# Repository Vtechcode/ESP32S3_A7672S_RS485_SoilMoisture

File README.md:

# ESP32-S3 + A7672S + RS485 Soil Moisture Node

A KiCad-designed IoT board that reads an RS485 soil sensor and sends the data over 4G LTE. It combines an **ESP32-S3** microcontroller, an **A7672SA** LTE Cat-1 modem with GNSS, and an **RS485** transceiver, all powered from a single DC input. It is built for remote soil monitoring in places with no Wi-Fi.

> **Status:** prototype, not yet fabricated or tested. <!-- TODO: update once boards arrive -->

## Features

- **ESP32-S3-WROOM-2** with Wi-Fi and Bluetooth LE, plus USB-C for programming and debugging
- **A7672SA** 4G LTE Cat-1 modem with GNSS, SIM socket, and two U.FL antenna connectors for LTE and GNSS, plus one more U.FL connector (BT_ANT) on the ESP32 side
- **RS485 interface** (MAX3485) on a screw terminal, with a 120 Ω termination switch and SM712 TVS surge protection
- **Three power rails** from one DC input: an LM2596S-5 buck converter (5 V), an AMS1117-3.3 LDO (3.3 V) for the ESP32 side, and a MIC29302 LDO (adjustable) for the modem supply (4V2)
- **Level shifting** between the ESP32 (3.3 V) and the modem (1.8 V) with a TXB0108
- **Protection:** ESD diodes on USB, SIM and RS485, plus TVS diodes on the supply
- **Usability:** reset and boot buttons, status LEDs, test points on the power rails, and 2×9 GPIO breakout headers
- **Assembly-friendly:** 2-layer board, all SMT parts on the top side, JLCPCB-compatible

## Block diagram

```
DC IN ──► LM2596S-5 ──► 5V ──┬─► AMS1117-3.3 ──► 3V3 ──► ESP32-S3 ◄── USB-C
                             └─► MIC29302 ─────► 4V2 ──► A7672SA ── SIM / LTE / GNSS
                                                              ▲
                              ESP32-S3 ◄─ TXB0108 (3V3↔1V8) ──┘
                                  │
                                  └─ UART ─► MAX3485 ─► RS485 terminal ─► soil sensor
```

## Layout

## Schematics

The design is split into four sheets.

**Power** (5 V buck, 3.3 V LDO, modem supply, protection)

**ESP32-S3** (module, USB-C, buttons, LEDs, GPIO headers)

**A7672S** (LTE modem, SIM, level shifter, antennas)

**RS485** (MAX3485, termination, surge protection)

## Target sensor

Designed for the **SenseCAP S-Temp&VWC&EC-02** soil sensor (temperature, volumetric water content and electrical conductivity) over RS485.

<!-- TODO: add sensor supply voltage, baud rate, and Modbus address/register map you use -->

## Repository layout

| Folder | Contents |
|---|---|
| `ESP32S3_A7672S_RS485_SoilMoisture/` | KiCad 9 project: schematics (`power`, `ESP32S3`, `A7672S`, `MAX485_RS485`) and PCB layout |
| `Mfr/` | Manufacturing files: Gerbers, drill files, BOM and CPL for JLCPCB |
| `images/` | Renders and screenshots |

## Board specifications

| | |
|---|---|
| Size | 81.5 × 111.3 mm |
| Layers | 2 |
| Assembly | Single-sided SMT (top), through-hole parts hand-soldered |
| Mounting | 4 × M3 holes |
| Design tool | KiCad 9 |

## Ordering the board

1. Upload the Gerber zip from `Mfr/` to JLCPCB.
2. Choose SMT assembly, top side, and upload the BOM and CPL.
3. Through-hole parts (screw terminals, pin headers, DIP switch) are not placed by SMT assembly. Solder them by hand or select JLCPCB's through-hole option.

## Getting started

<!-- TODO: fill in once firmware exists -->
1. Connect the DC supply to the power screw terminal. <!-- TODO: state the input voltage range -->
2. Insert a SIM card and attach the LTE and GNSS antennas **before** powering on.
3. Wire the soil sensor to the RS485 terminal (A, B, GND and sensor supply).
4. Connect USB-C to flash the ESP32-S3.

## Pin assignments

<!-- TODO: add a table of ESP32-S3 GPIOs for modem UART, modem power key/reset, RS485 TX/RX/DE, LEDs -->

## Firmware

<!-- TODO: link firmware repo or describe planned stack (ESP-IDF / Arduino, AT-command library, Modbus library, MQTT/HTTP endpoint) -->

## License

<!-- TODO: choose one, e.g. CERN-OHL-P-2.0 for hardware, MIT for firmware -->

## Author

Victor Waburi ([@Vtechcode](https://github.com/Vtechcode))

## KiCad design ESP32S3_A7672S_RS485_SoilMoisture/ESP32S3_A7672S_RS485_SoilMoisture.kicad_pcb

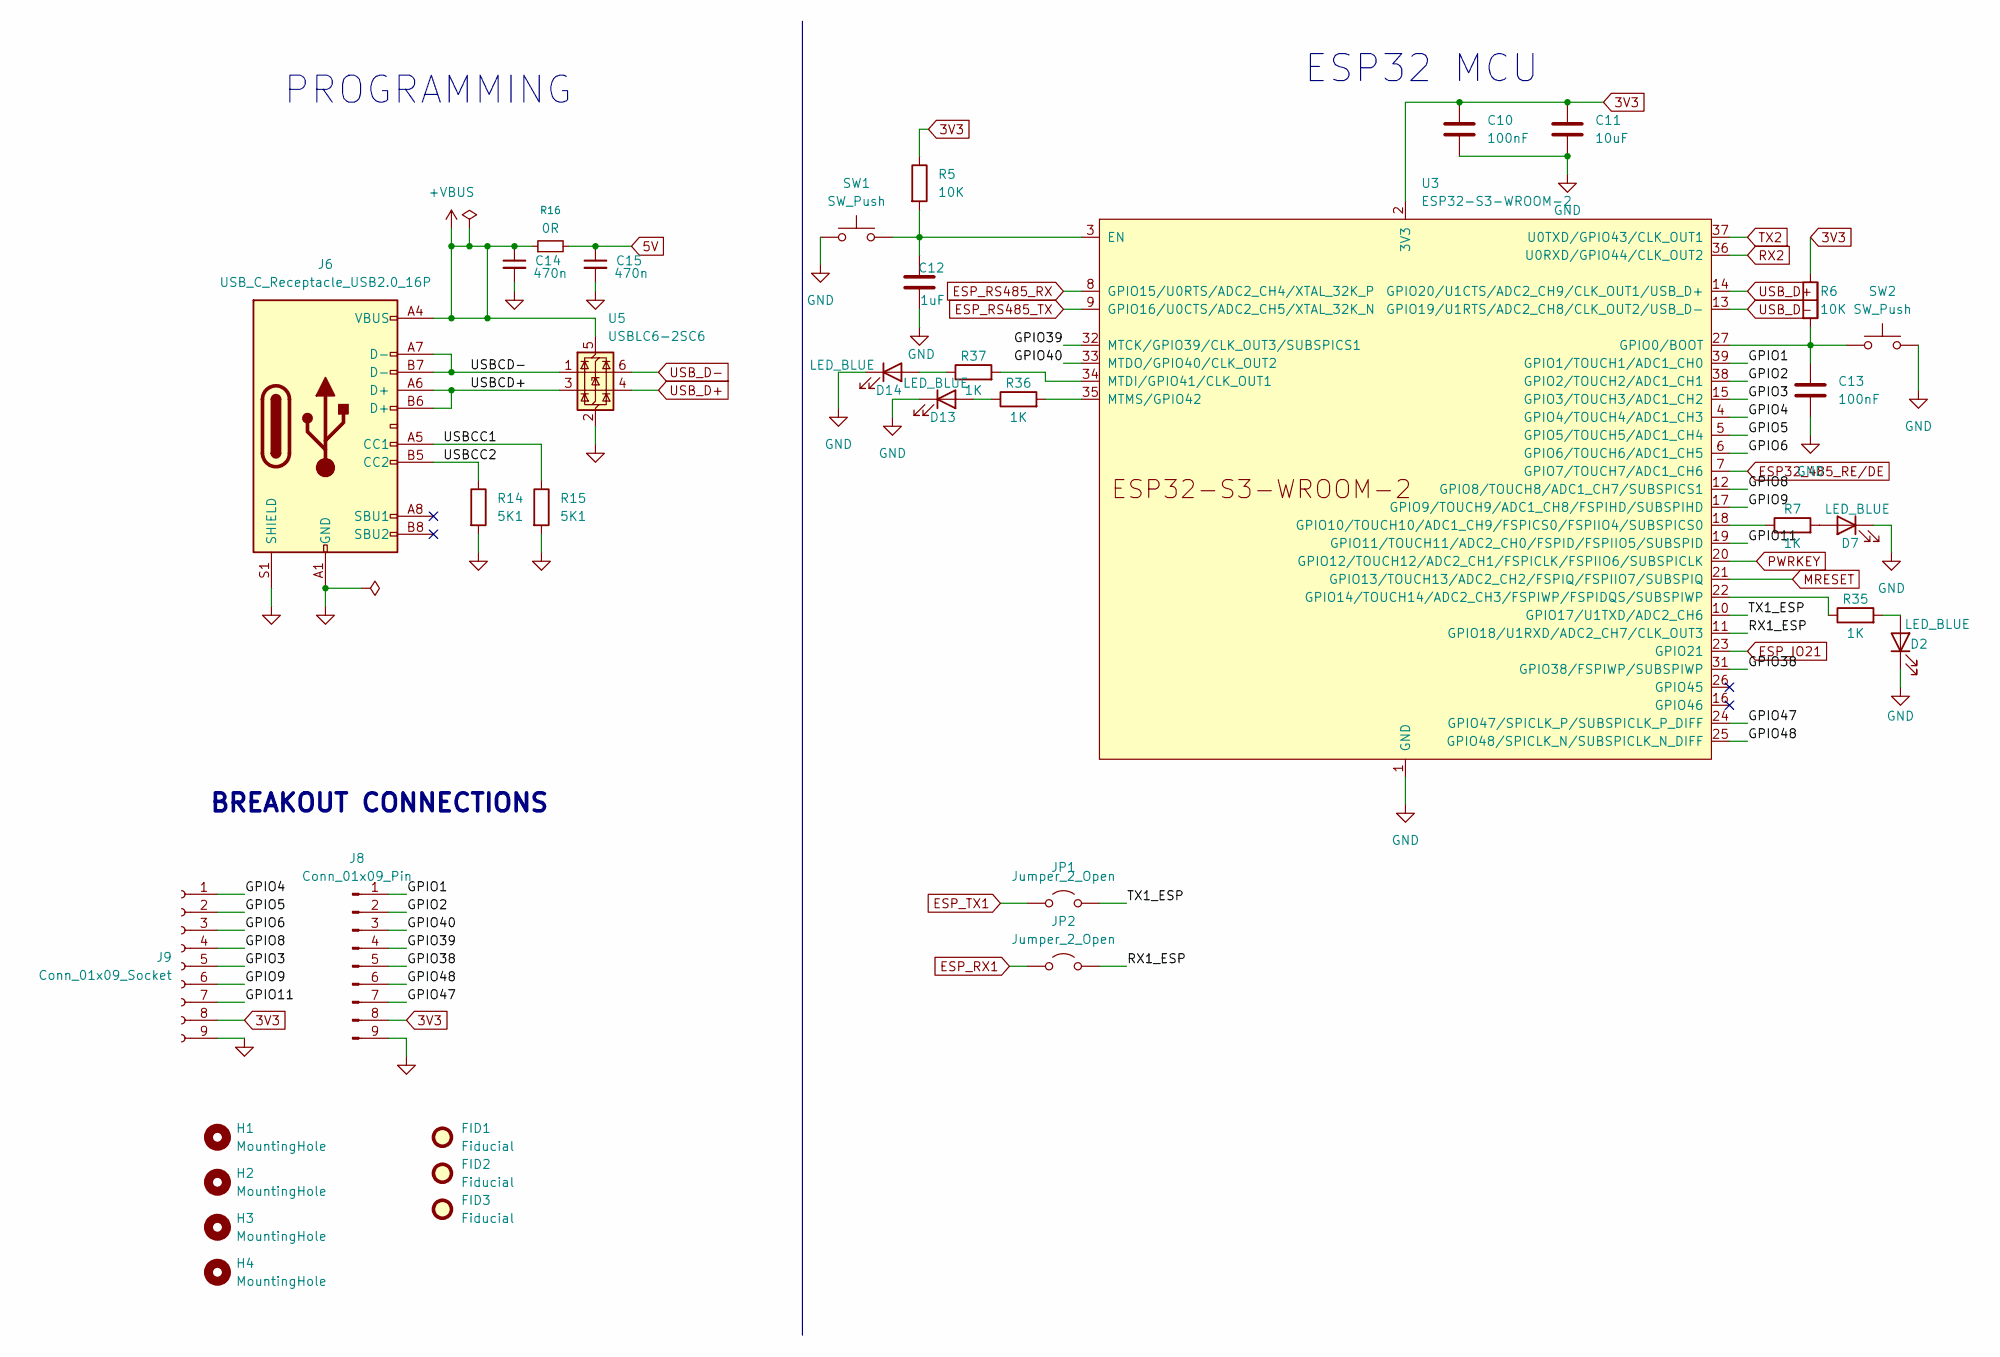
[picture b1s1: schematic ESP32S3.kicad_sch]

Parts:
C10, C13: 100nF; C_0603_1608Metric_Pad1.08x0.95mm_HandSolder; LCSC number C16194197
C11: 10uF; C_0603_1608Metric_Pad1.08x0.95mm_HandSolder; LCSC number C109457
C12: 1uF; C_0603_1608Metric_Pad1.08x0.95mm_HandSolder; LCSC number C29936
C14, C15: 470n; C_0402_1005Metric; LCSC number C364319
D2, D7, D13, D14: LED_BLUE; LED_0805_2012Metric_Pad1.15x1.40mm_HandSolder; LCSC number C5156165
FID1, FID2, FID3: Fiducial; Fiducial_0.5mm_Mask1.5mm
H1, H2, H3, H4: MountingHole; MountingHole_3.2mm_M3
J6: USB_C_Receptacle_USB2.0_16P; USB_C_Receptacle_GCT_USB4105-xx-A_16P_TopMnt_Horizontal; LCSC number C45082766
J8: Conn_01x09_Pin; PinSocket_1x09_P2.54mm_Vertical
J9: Conn_01x09_Socket; PinSocket_1x09_P2.54mm_Vertical
JP1, JP2: Jumper_2_Open; TestPoint_2Pads_Pitch2.54mm_Drill0.8mm
R5, R6: 10K; R_0603_1608Metric_Pad0.98x0.95mm_HandSolder; LCSC number C2479067
R7, R35, R36, R37: 1K; R_0603_1608Metric_Pad0.98x0.95mm_HandSolder; LCSC number C860716
R14: 5K1; R_0603_1608Metric_Pad0.98x0.95mm_HandSolder; LCSC number C123727
R15: 5K1; R_0402_1005Metric; LCSC number C123727
R16: 0R; R_0603_1608Metric; LCSC number C100044
SW1, SW2: SW_Push; SW_SPST_B3U-1000P; LCSC number C428628
U3: ESP32-S3-WROOM-2; LCSC number C42417293
U5: USBLC6-2SC6; SOT-23-6; LCSC number C7519

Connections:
3V3: C10.1, C11.1, J8.8, J9.8, R5.1, R6.1, U3.2 (3V3); also elsewhere on the board
5V: C15.1, R16.2; also elsewhere on the board
+VBUS: C14.1, J6.A4 (VBUS), J6.A9 (VBUS), J6.B4 (VBUS), J6.B9 (VBUS), R16.1, U5.5 (VBUS)
/ESP32S3/GPIO1: J8.1, U3.39 (GPIO1/TOUCH1/ADC1_CH0)
/ESP32S3/GPIO2: J8.2, U3.38 (GPIO2/TOUCH2/ADC1_CH1)
/ESP32S3/GPIO3: J9.5, U3.15 (GPIO3/TOUCH3/ADC1_CH2)
/ESP32S3/GPIO4: J9.1, U3.4 (GPIO4/TOUCH4/ADC1_CH3)
/ESP32S3/GPIO5: J9.2, U3.5 (GPIO5/TOUCH5/ADC1_CH4)
/ESP32S3/GPIO6: J9.3, U3.6 (GPIO6/TOUCH6/ADC1_CH5)
/ESP32S3/GPIO8: J9.4, U3.12 (GPIO8/TOUCH8/ADC1_CH7/SUBSPICS1)
/ESP32S3/GPIO9: J9.6, U3.17 (GPIO9/TOUCH9/ADC1_CH8/FSPIHD/SUBSPIHD)
/ESP32S3/GPIO11: J9.7, U3.19 (GPIO11/TOUCH11/ADC2_CH0/FSPID/FSPIIO5/S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)
/ESP32S3/GPIO38: J8.5, U3.31 (GPIO38/FSPIWP/SUBSPIWP)
/ESP32S3/GPIO39: J8.4, U3.32 (MTCK/GPIO39/CLK_OUT3/SUBSPICS1)
/ESP32S3/GPIO40: J8.3, U3.33 (MTDO/GPIO40/CLK_OUT2)
/ESP32S3/GPIO47: J8.7, U3.24 (GPIO47/SPICLK_P/SUBSPICLK_P_DIFF)
/ESP32S3/GPIO48: J8.6, U3.25 (GPIO48/SPICLK_N/SUBSPICLK_N_DIFF)
/ESP32S3/RX1_ESP: JP2.2 (B), U3.11 (GPIO18/U1RXD/ADC2_CH7/CLK_OUT3)
/ESP32S3/TX1_ESP: JP1.2 (B), U3.10 (GPIO17/U1TXD/ADC2_CH6)
/ESP32S3/USBCC1: J6.A5 (CC1), R15.1
/ESP32S3/USBCC2: J6.B5 (CC2), R14.1
/ESP32S3/USBCD+: J6.A6 (D+), J6.B6 (D+), U5.3 (I/O2)
/ESP32S3/USBCD-: J6.A7 (D-), J6.B7 (D-), U5.1 (I/O1)
ESP32_485_RE/DE: U3.7 (GPIO7/TOUCH7/ADC1_CH6); also elsewhere on the board
ESP_IO21: U3.23 (GPIO21); also elsewhere on the board
ESP_RS485_RX: U3.8 (GPIO15/U0RTS/ADC2_CH4/XTAL_32K_P); also elsewhere on the board
ESP_RS485_TX: U3.9 (GPIO16/U0CTS/ADC2_CH5/XTAL_32K_N); also elsewhere on the board
ESP_RX1: JP2.1 (A); also elsewhere on the board
ESP_TX1: JP1.1 (A); also elsewhere on the board
GND: C10.2, C11.2, C12.2, C13.2, C14.2, C15.2, D2.1 (K), D7.1 (K), D13.1 (K), D14.1 (K), J6.A1 (GND), J6.A12 (GND), J6.B1 (GND), J6.B12 (GND), J6.S1 (SHIELD), J8.9, J9.9, R14.2, R15.2, SW1.1, SW2.2, U3.1 (GND), U3.40 (GND), U3.41 (GND), U5.2 (GND); also elsewhere on the board
MRESET: U3.21 (GPIO13/TOUCH13/ADC2_CH2/FSPIQ/FSPIIO7/S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); also elsewhere on the board
unnamed: D2.2 (A), R35.2
unnamed: D7.2 (A), R7.2
unnamed: D13.2 (A), R36.1
unnamed: D14.2 (A), R37.1
unnamed: C12.1, R5.2, SW1.2, U3.3 (EN)
unnamed: C13.1, R6.2, SW2.1, U3.27 (GPIO0/BOOT)
unnamed: R7.1, U3.18 (GPIO10/TOUCH10/ADC1_CH9/FSPICS0/FSPIIO4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)
unnamed: R35.1, U3.22 (GPIO14/TOUCH14/ADC2_CH3/FSPIWP/FSPIDQS/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)
unnamed: R37.2, U3.34 (MTDI/GPIO41/CLK_OUT1)
unnamed: R36.2, U3.35 (MTMS/GPIO42)
PWRKEY: U3.20 (GPIO12/TOUCH12/ADC2_CH1/FSPICLK/FSPIIO6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); also elsewhere on the board
RX2: U3.36 (U0RXD/GPIO44/CLK_OUT2); also elsewhere on the board
TX2: U3.37 (U0TXD/GPIO43/CLK_OUT1); also elsewhere on the board
USB_D+: U3.14 (GPIO20/U1CTS/ADC2_CH9/CLK_OUT1/USB_D+), U5.4 (I/O2)
USB_D-: U3.13 (GPIO19/U1RTS/ADC2_CH8/CLK_OUT2/USB_D-), U5.6 (I/O1)

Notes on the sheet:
ESP32 MCU
BREAKOUT CONNECTIONS
PROGRAMMING

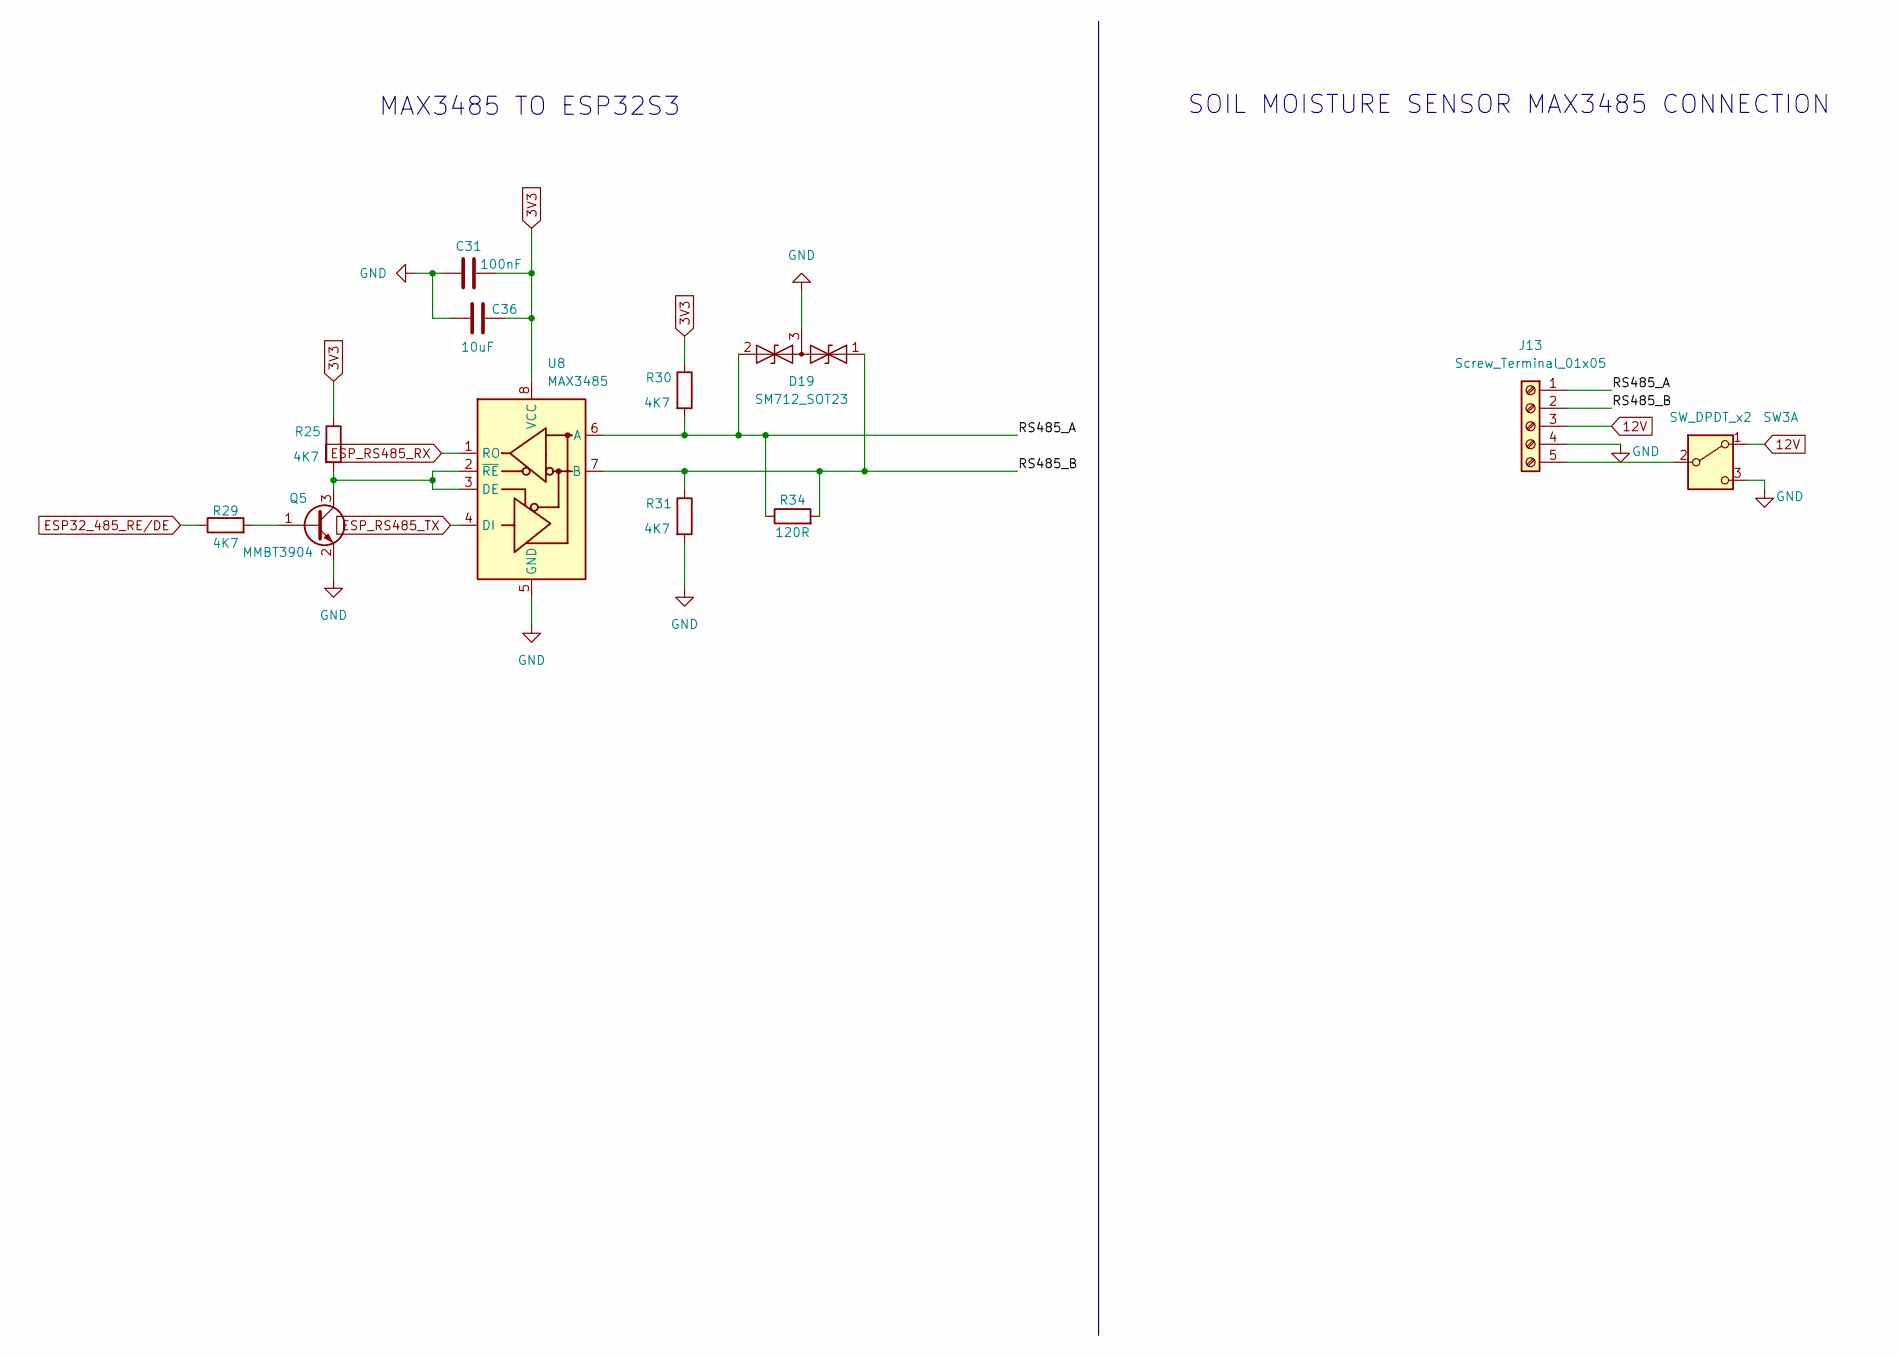
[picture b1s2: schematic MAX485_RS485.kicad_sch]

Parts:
C31: 100nF; C_0603_1608Metric; LCSC number C16194197
C36: 10uF; C_0603_1608Metric; LCSC number C109457
D19: SM712_SOT23; SOT-23; LCSC number C502564
J13: Screw_Terminal_01x05; TerminalBlock_Phoenix_MKDS-1,5-5-5.08_1x05_P5.08mm_Horizont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
Q5: MMBT3904; SOT-23; LCSC number C81464
R25, R29, R30, R31: 4K7; R_0603_1608Metric_Pad0.98x0.95mm_HandSolder; LCSC number C844931
R34: 120R; R_0603_1608Metric_Pad0.98x0.95mm_HandSolder; LCSC number C4307692
SW3: SW_DPDT_x2; SW_CK_JS202011CQN_DPDT_Straight; LCSC number C221663
U8: MAX3485; SOIC-8_3.9x4.9mm_P1.27mm; LCSC number C94609

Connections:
3V3: C31.2, C36.2, R25.1, R30.1, U8.8 (VCC); also elsewhere on the board
12V: J13.3, SW3.1 (A); also elsewhere on the board
/MAX485_RS485/RS485_A: D19.2 (A2), J13.1, R30.2, R34.1, U8.6 (A)
/MAX485_RS485/RS485_B: D19.1 (A1), J13.2, R31.1, R34.2, U8.7 (B)
ESP32_485_RE/DE: R29.1; also elsewhere on the board
ESP_RS485_RX: U8.1 (RO); also elsewhere on the board
ESP_RS485_TX: U8.4 (DI); also elsewhere on the board
GND: C31.1, C36.1, D19.3 (common), J13.4, Q5.2 (E), R31.2, SW3.3 (C), U8.5 (GND); also elsewhere on the board
unnamed: J13.5, SW3.2 (B)
unnamed: Q5.1 (B), R29.2
unnamed: Q5.3 (C), R25.2, U8.2 (~RE), U8.3 (DE)

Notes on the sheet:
MAX3485 TO ESP32S3
SOIL MOISTURE SENSOR MAX3485 CONNECTION

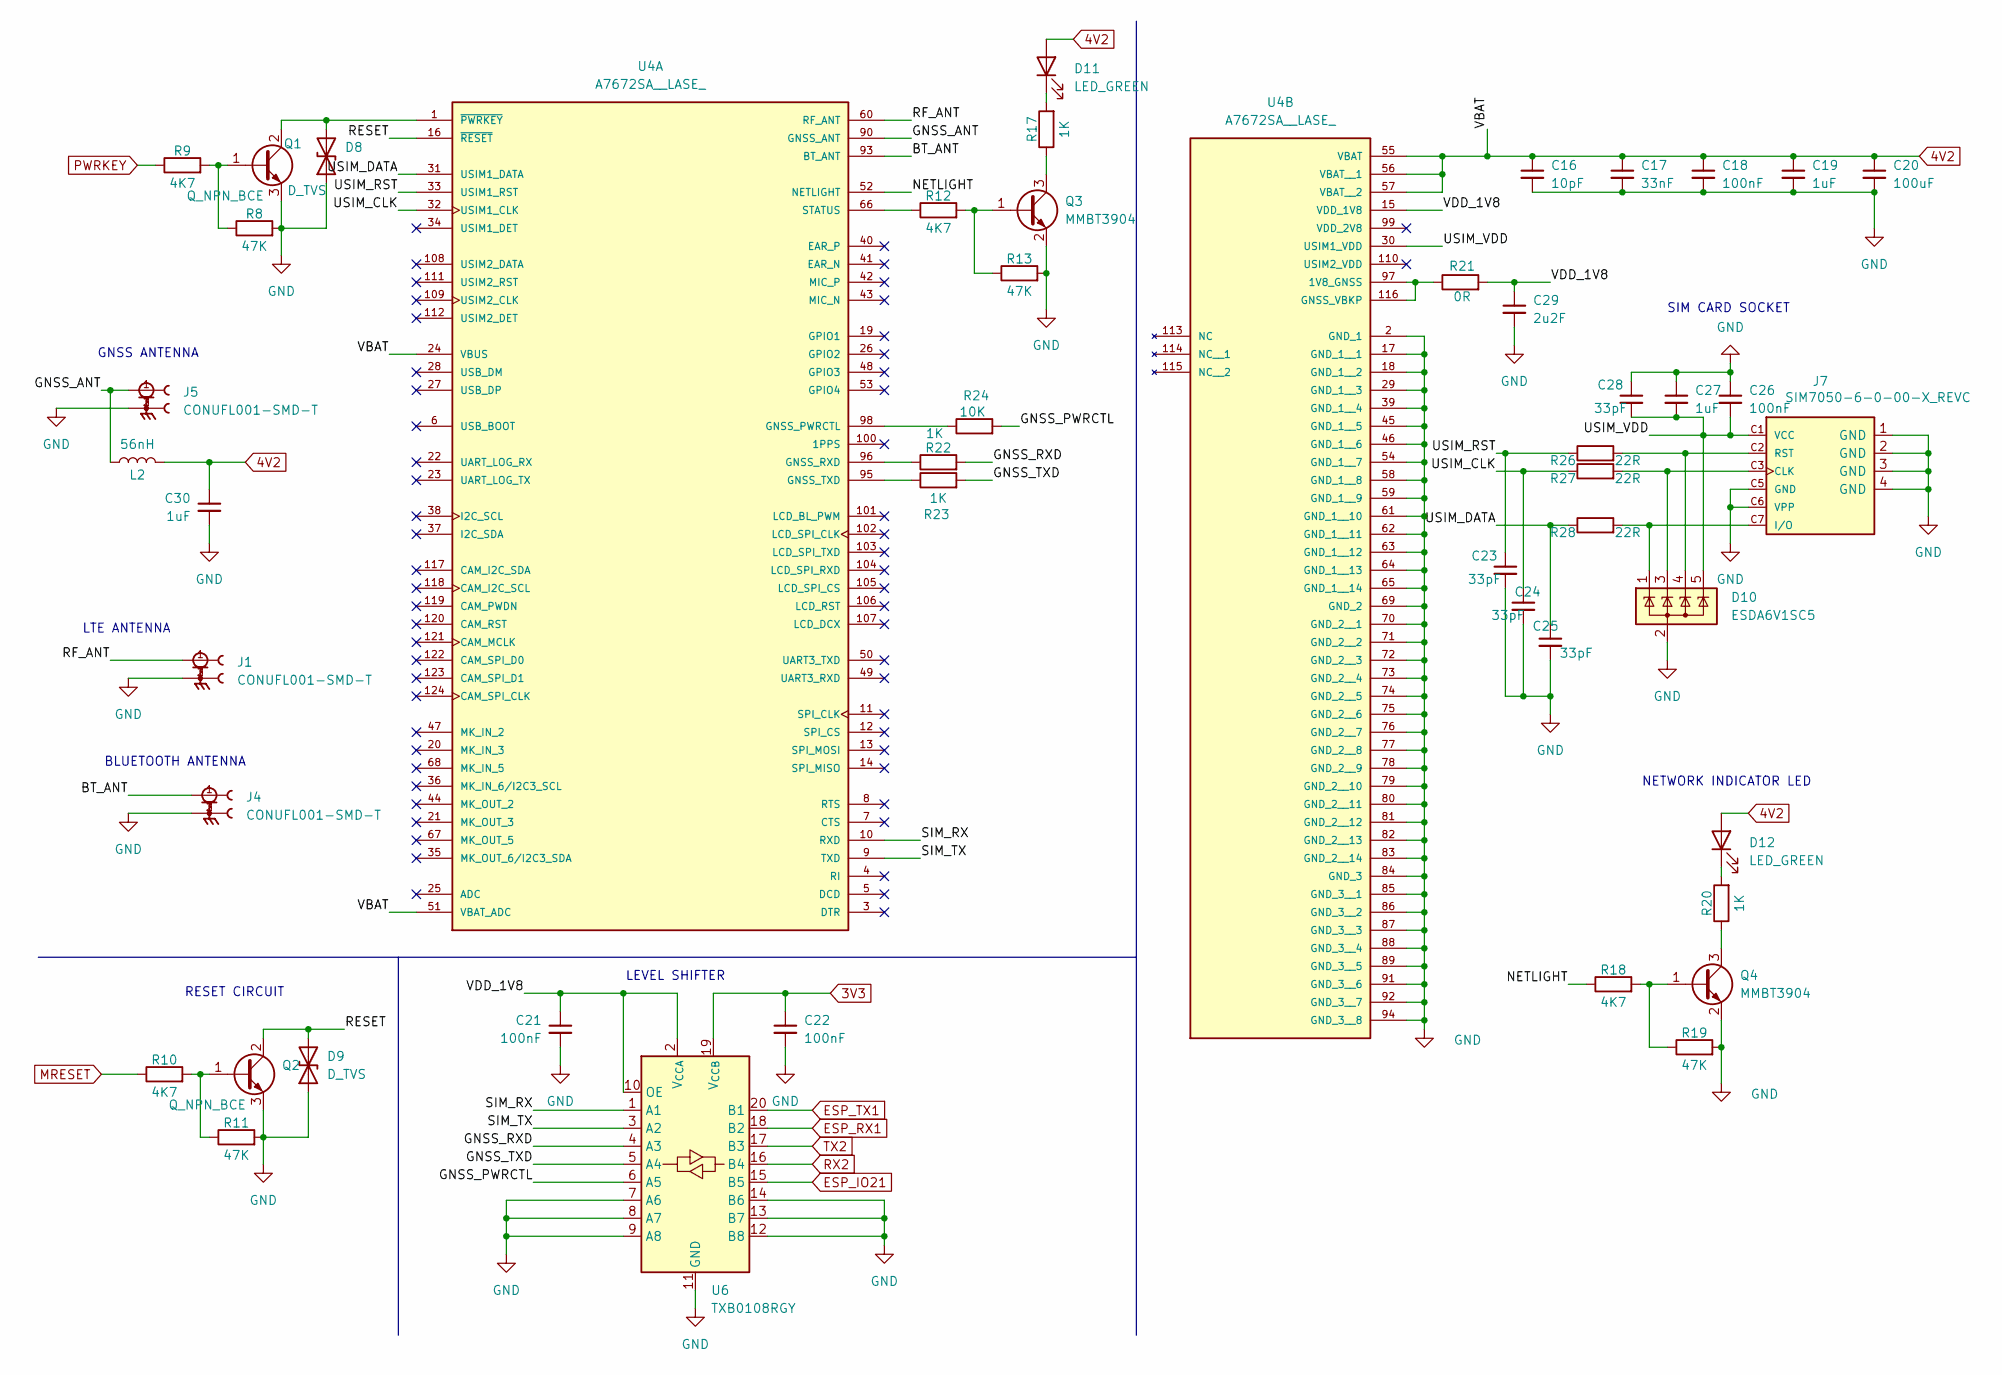
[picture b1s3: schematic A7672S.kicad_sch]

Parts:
C16: 10pF; C_0603_1608Metric_Pad1.08x0.95mm_HandSolder; LCSC number C2167326
C17: 33nF; C_0603_1608Metric_Pad1.08x0.95mm_HandSolder; LCSC number C16194260
C18: 100nF; C_0603_1608Metric_Pad1.08x0.95mm_HandSolder; LCSC number C16194197
C19: 1uF; C_0603_1608Metric_Pad1.08x0.95mm_HandSolder; LCSC number C29936
C20: 100uF; C_0805_2012Metric; LCSC number C141660
C21, C22, C26: 100nF; C_0603_1608Metric; LCSC number C16194197
C23, C24, C25, C28: 33pF; C_0603_1608Metric; LCSC number C1663
C27, C30: 1uF; C_0603_1608Metric; LCSC number C29936
C29: 2u2F; C_0603_1608Metric_Pad1.08x0.95mm_HandSolder; LCSC number C23630
D8, D9: D_TVS; D_SOD-323; LCSC number C5173266
D10: ESDA6V1SC5; SOT-23-5; LCSC number C2935146
D11, D12: LED_GREEN; LED_0805_2012Metric_Pad1.15x1.40mm_HandSolder; LCSC number C5456999
J1, J4, J5: CONUFL001-SMD-T; LINX_CONUFL001-SMD-T; LCSC number C22418213
J7: SIM7050-6-0-00-X_REVC; GCT_SIM7050-6-0-00-X_REVC; LCSC number C7363806
L2: 56nH; L_0603_1608Metric; LCSC number C98079
Q1, Q2: Q_NPN_BCE; SOT-23; LCSC number C513268
Q3, Q4: MMBT3904; SOT-23; LCSC number C81464
R8, R11, R13, R19: 47K; R_0603_1608Metric_Pad0.98x0.95mm_HandSolder; LCSC number C105579
R9, R10, R12, R18: 4K7; R_0603_1608Metric_Pad0.98x0.95mm_HandSolder; LCSC number C844931
R17, R20, R23: 1K; R_0603_1608Metric_Pad0.98x0.95mm_HandSolder; LCSC number C860716
R21: 0R; R_0805_2012Metric_Pad1.20x1.40mm_HandSolder; LCSC number C100045
R22: 1K; R_0603_1608Metric; LCSC number C98079
R24: 10K; R_0603_1608Metric_Pad0.98x0.95mm_HandSolder; LCSC number C2479067
R26, R27, R28: 22R; R_0603_1608Metric; LCSC number C2479410
U4: A7672SA__LASE_; XCVR_A7672SA__LASE_; PARTREV 1.03; LCSC number C5370391
U6: TXB0108RGY; Texas_RGY_R-PVQFN-N20_EP2.05x3.05mm; LCSC number C194701

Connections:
3V3: C22.1, U6.19 (V_{CCB}); also elsewhere on the board
4V2: C16.1, C17.1, C18.1, C19.1, C20.1, C30.1, D11.2 (A), D12.2 (A), L2.2, U4.24 (VBUS), U4.51 (VBAT_ADC), U4.55 (VBAT), U4.56 (VBAT__1), U4.57 (VBAT__2); also elsewhere on the board
/A7672S/BT_ANT: J4.1, U4.93 (BT_ANT)
/A7672S/GNSS_ANT: J5.1, L2.1, U4.90 (GNSS_ANT)
/A7672S/GNSS_PWRCTL: R24.2, U6.6 (A5)
/A7672S/GNSS_RXD: R22.2, U6.4 (A3)
/A7672S/GNSS_TXD: R23.2, U6.5 (A4)
/A7672S/NETLIGHT: R18.1, U4.52 (NETLIGHT)
/A7672S/RESET: D9.2 (A2), Q2.2 (C), U4.16 (~RESET)
/A7672S/RF_ANT: J1.1, U4.60 (RF_ANT)
/A7672S/SIM_RX: U4.10 (RXD), U6.1 (A1)
/A7672S/SIM_TX: U4.9 (TXD), U6.3 (A2)
/A7672S/USIM_CLK: C24.1, R27.1, U4.32 (USIM1_CLK)
/A7672S/USIM_DATA: C25.1, R28.1, U4.31 (USIM1_DATA)
/A7672S/USIM_RST: C23.1, R26.1, U4.33 (USIM1_RST)
/A7672S/USIM_VDD: C26.2, C27.2, C28.2, D10.5 (K), J7.C1 (VCC), U4.30 (USIM1_VDD)
/A7672S/VDD_1V8: C21.1, C29.1, R21.2, U4.15 (VDD_1V8), U6.2 (V_{CCA}), U6.10 (OE)
ESP_IO21: U6.15 (B5); also elsewhere on the board
ESP_RX1: U6.18 (B2); also elsewhere on the board
ESP_TX1: U6.20 (B1); also elsewhere on the board
GND: C16.2, C17.2, C18.2, C19.2, C20.2, C21.2, C22.2, C23.2, C24.2, C25.2, C26.1, C27.1, C28.1, C29.2, C30.2, D8.1 (A1), D9.1 (A1), D10.2 (A), J1.2, J1.3, J4.2, J4.3, J5.2, J5.3, J7.1 (GND), J7.2 (GND), J7.3 (GND), J7.4 (GND), J7.C5 (GND), J7.C6 (VPP), Q1.3 (E), Q2.3 (E), Q3.2 (E), Q4.2 (E), R8.2, R11.2, R13.2, R19.2, U4.2 (GND_1), U4.17 (GND_1__1), U4.18 (GND_1__2), U4.29 (GND_1__3), U4.39 (GND_1__4), U4.45 (GND_1__5), U4.46 (GND_1__6), U4.54 (GND_1__7), U4.58 (GND_1__8), U4.59 (GND_1__9), U4.61 (GND_1__10), U4.62 (GND_1__11), U4.63 (GND_1__12), U4.64 (GND_1__13), U4.65 (GND_1__14), U4.69 (GND_2), U4.70 (GND_2__1), U4.71 (GND_2__2), U4.72 (GND_2__3), U4.73 (GND_2__4), U4.74 (GND_2__5), U4.75 (GND_2__6), U4.76 (GND_2__7), U4.77 (GND_2__8), U4.78 (GND_2__9), U4.79 (GND_2__10), U4.80 (GND_2__11), U4.81 (GND_2__12), U4.82 (GND_2__13), U4.83 (GND_2__14), U4.84 (GND_3), U4.85 (GND_3__1), U4.86 (GND_3__2), U4.87 (GND_3__3), U4.88 (GND_3__4), U4.89 (GND_3__5), U4.91 (GND_3__6), U4.92 (GND_3__7), U4.94 (GND_3__8), U6.7 (A6), U6.8 (A7), U6.9 (A8), U6.11 (GND), U6.12 (B8), U6.13 (B7), U6.14 (B6), U6.21 (GND); also elsewhere on the board
MRESET: R10.1; also elsewhere on the board
unnamed: D8.2 (A2), Q1.2 (C), U4.1 (~PWRKEY)
unnamed: D11.1 (K), R17.2
unnamed: D12.1 (K), R20.2
unnamed: D10.3 (K), J7.C3 (CLK), R27.2
unnamed: D10.1 (K), J7.C7 (I/O), R28.2
unnamed: D10.4 (K), J7.C2 (RST), R26.2
unnamed: Q1.1 (B), R8.1, R9.2
unnamed: Q2.1 (B), R10.2, R11.1
unnamed: Q3.1 (B), R12.2, R13.1
unnamed: Q3.3 (C), R17.1
unnamed: Q4.1 (B), R18.2, R19.1
unnamed: Q4.3 (C), R20.1
unnamed: R24.1, U4.98 (GNSS_PWRCTL)
unnamed: R22.1, U4.96 (GNSS_RXD)
unnamed: R23.1, U4.95 (GNSS_TXD)
unnamed: R12.1, U4.66 (STATUS)
unnamed: R21.1, U4.97 (1V8_GNSS), U4.116 (GNSS_VBKP)
PWRKEY: R9.1; also elsewhere on the board
RX2: U6.16 (B4); also elsewhere on the board
TX2: U6.17 (B3); also elsewhere on the board

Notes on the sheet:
LTE ANTENNA
NETWORK INDICATOR LED
GNSS ANTENNA
SIM CARD SOCKET
RESET CIRCUIT
LEVEL SHIFTER
BLUETOOTH ANTENNA

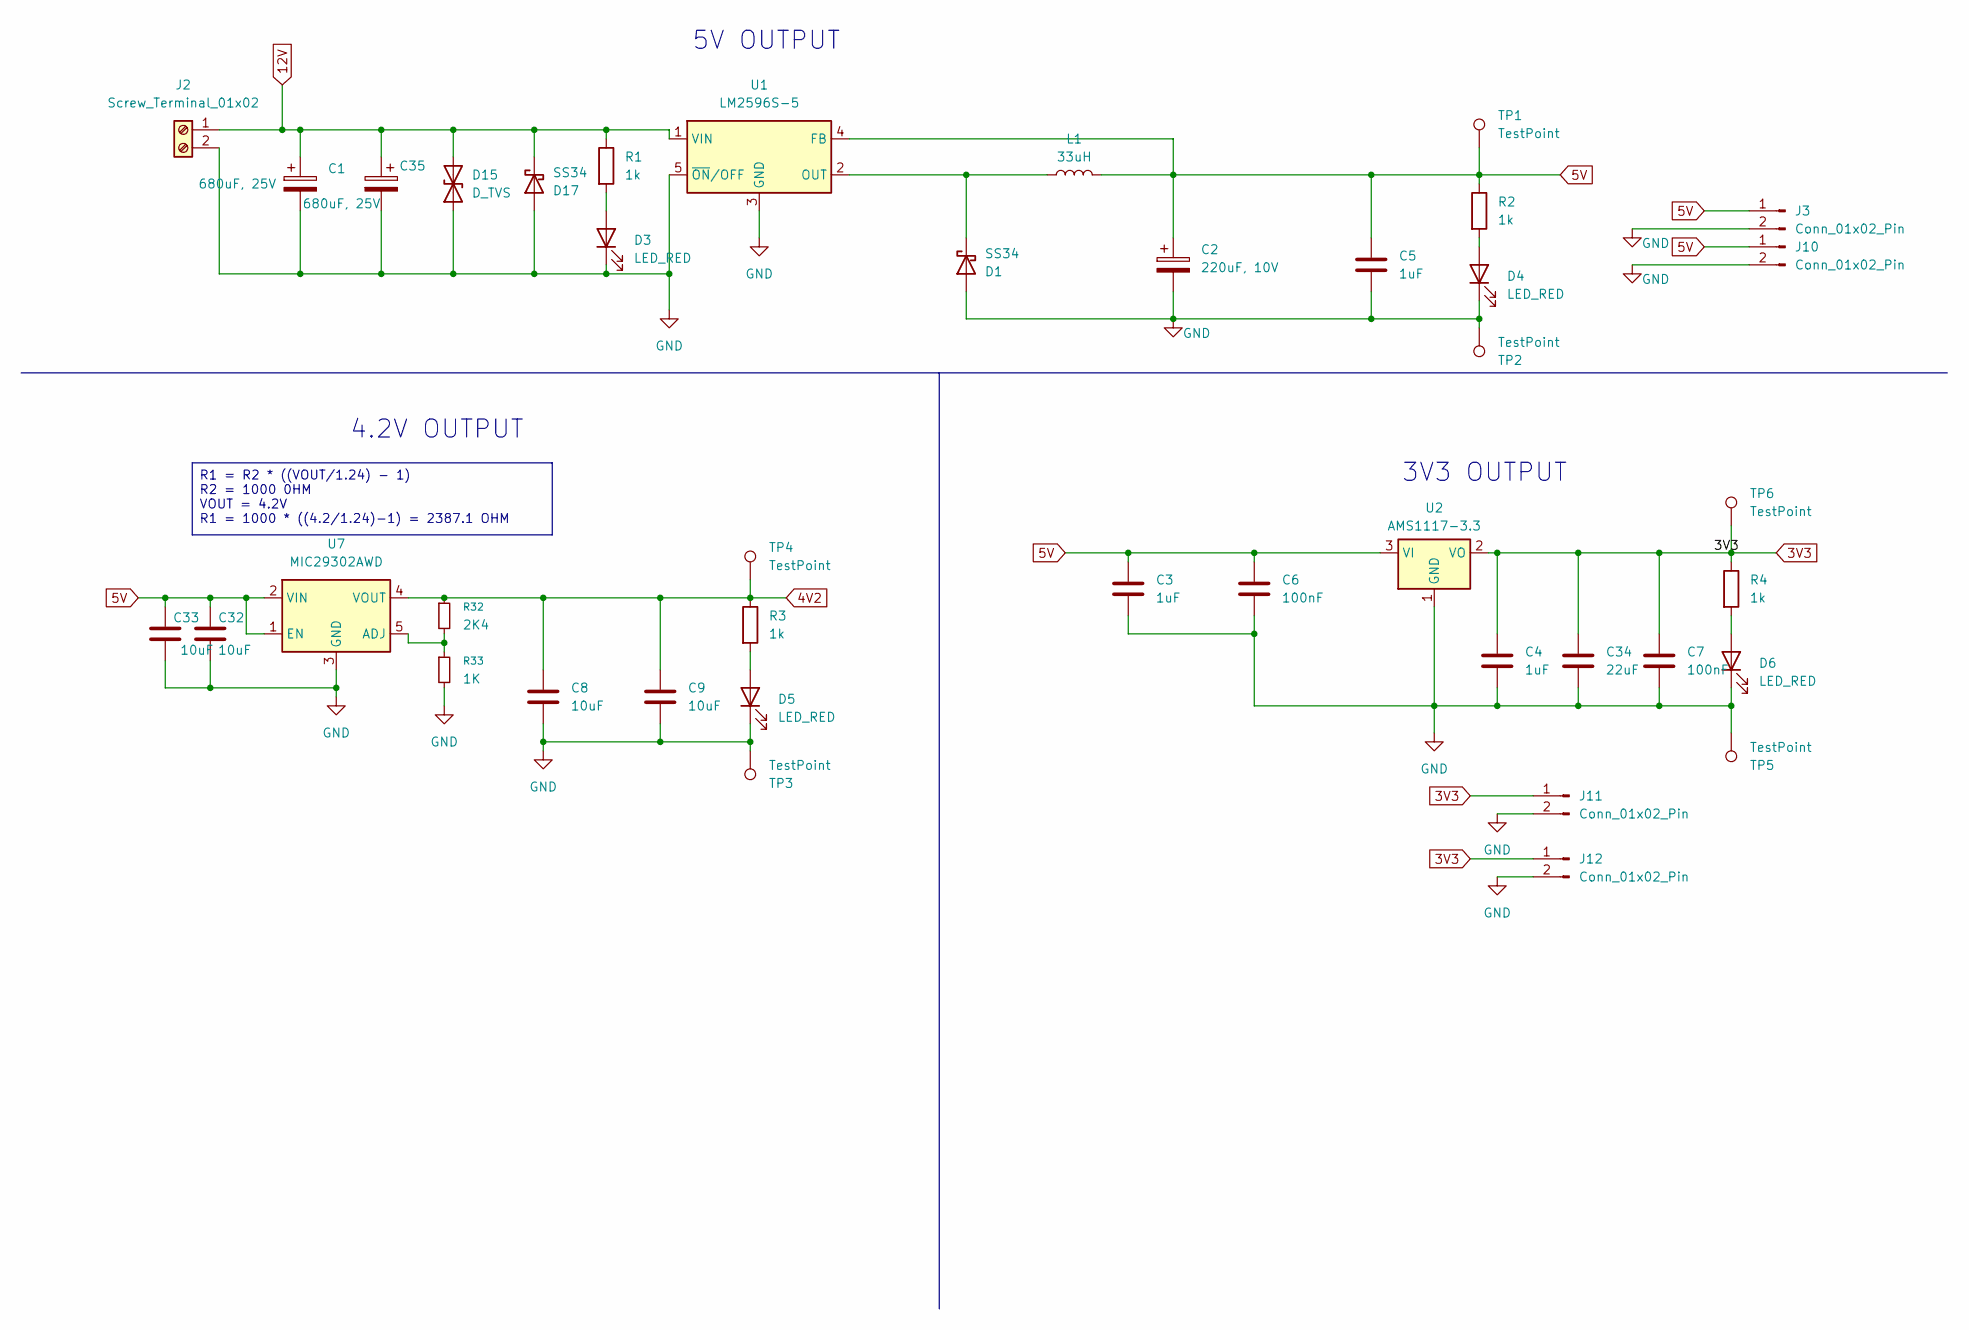
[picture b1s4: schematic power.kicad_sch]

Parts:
C1, C35: 680uF, 25V; CP_Elec_10x7.7; LCSC number C494831
C2: 220uF, 10V; CP_Elec_6.3x7.7; LCSC number C336207
C3, C4, C5: 1uF; C_0603_1608Metric_Pad1.08x0.95mm_HandSolder; LCSC number C29936
C6, C7: 100nF; C_0603_1608Metric_Pad1.08x0.95mm_HandSolder; LCSC number C16194197
C8, C9, C32, C33: 10uF; C_0603_1608Metric_Pad1.08x0.95mm_HandSolder; LCSC number C109457
C34: 22uF; C_0805_2012Metric; LCSC number C128856
D1, D17: SS34; D_SMC; LCSC number C2837271
D3, D4, D5, D6: LED_RED; LED_0805_2012Metric; LCSC number C17440976
D15: D_TVS; D_SOD-128; LCSC number VS12VUA1LAMTR
J2: Screw_Terminal_01x02; TerminalBlock_Phoenix_MKDS-1,5-2-5.08_1x02_P5.08mm_Horizont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; LCSC number C8465
J3, J10, J11, J12: Conn_01x02_Pin; PinHeader_1x02_P2.54mm_Vertical
L1: 33uH; L_7.3x7.3_H4.5; LCSC number C2042589
R1, R2, R3, R4: 1k; R_0603_1608Metric; LCSC number C860716
R32: 2K4; R_0603_1608Metric_Pad0.98x0.95mm_HandSolder; LCSC number C543157
R33: 1K; R_0603_1608Metric_Pad0.98x0.95mm_HandSolder; LCSC number C860716
TP1, TP2, TP3, TP4, TP5, TP6: TestPoint; TestPoint_Pad_D2.0mm
U1: LM2596S-5; TO-263-5_TabPin3; LCSC number C116713
U2: AMS1117-3.3; SOT-223-3_TabPin2; LCSC number C9662
U7: MIC29302AWD; TO-252-5_TabPin3; LCSC number C478084

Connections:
3V3: C4.1, C7.1, C34.1, J11.1, J12.1, R4.1, TP6.1, U2.2 (VO); also elsewhere on the board
4V2: C8.1, C9.1, R3.1, R32.1, TP4.1, U7.4 (VOUT); also elsewhere on the board
5V: C2.1, C3.1, C5.1, C6.1, C32.1, C33.1, J3.1, J10.1, L1.2, R2.1, TP1.1, U1.4 (FB), U2.3 (VI), U7.1 (EN), U7.2 (VIN); also elsewhere on the board
12V: C1.1, C35.1, D15.2 (A2), D17.1 (K), J2.1, R1.1, U1.1 (VIN); also elsewhere on the board
GND: C1.2, C2.2, C3.2, C4.2, C5.2, C6.2, C7.2, C8.2, C9.2, C32.2, C33.2, C34.2, C35.2, D1.2 (A), D3.1 (K), D4.1 (K), D5.1 (K), D6.1 (K), D15.1 (A1), D17.2 (A), J2.2, J3.2, J10.2, J11.2, J12.2, R33.2, TP2.1, TP3.1, TP5.1, U1.3 (GND), U1.5 (~ON/OFF), U2.1 (GND), U7.3 (GND); also elsewhere on the board
unnamed: D1.1 (K), L1.1, U1.2 (OUT)
unnamed: D3.2 (A), R1.2
unnamed: D4.2 (A), R2.2
unnamed: D5.2 (A), R3.2
unnamed: D6.2 (A), R4.2
unnamed: R32.2, R33.1, U7.5 (ADJ)

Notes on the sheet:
4.2V OUTPUT
5V OUTPUT
3V3 OUTPUT
R1 = R2 * ((VOUT/1.24) - 1) R2 = 1000 0HM VOUT = 4.2V R1 = 1000 * ((4.2/1.24)-1) = 2387.1 OHM

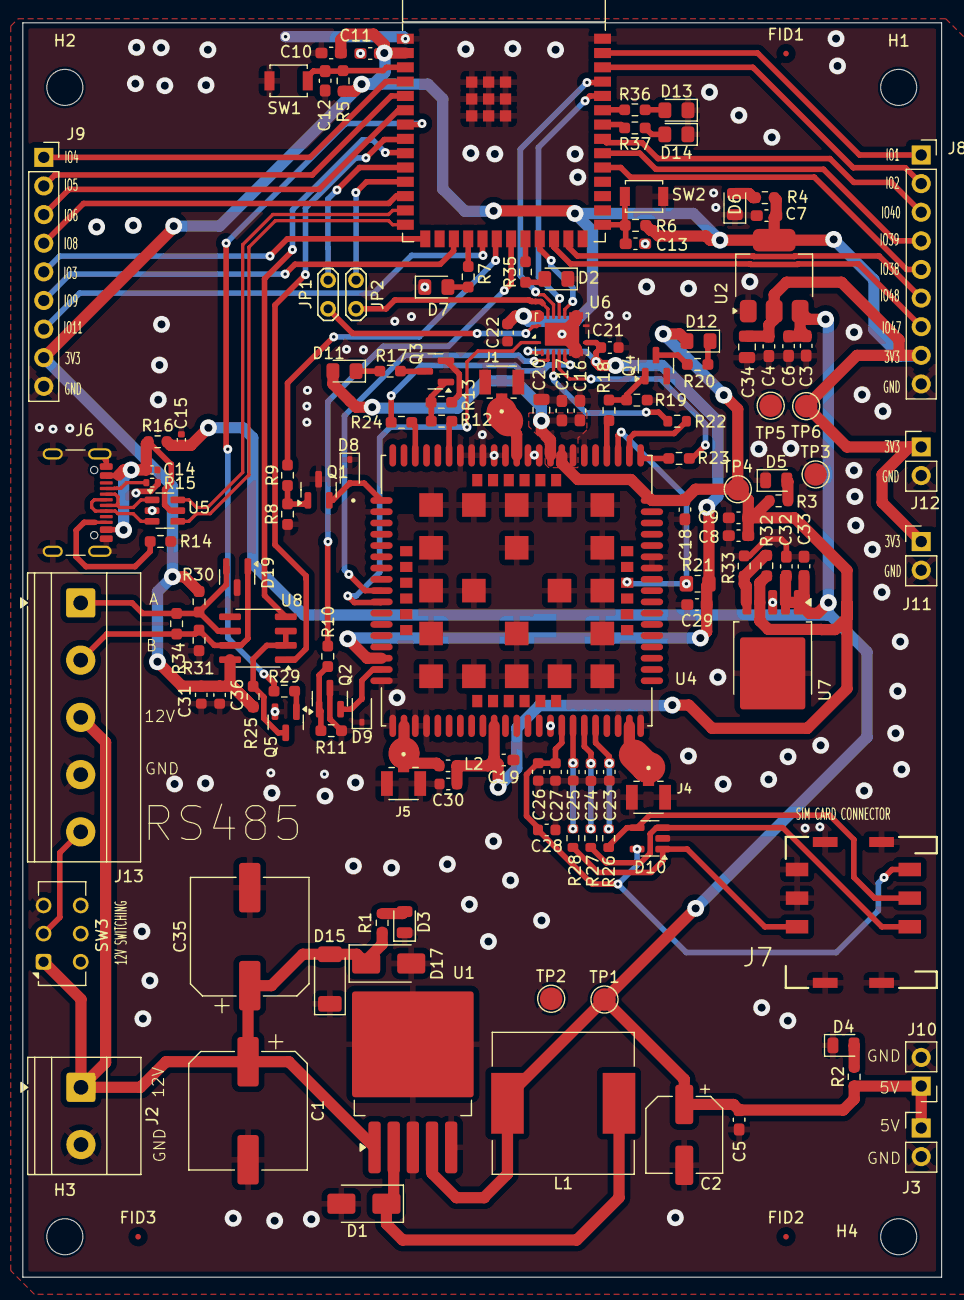
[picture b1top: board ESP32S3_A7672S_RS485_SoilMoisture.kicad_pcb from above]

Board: 2 copper layers, 81.5 x 111.3 mm, 136 parts (0 on the bottom side), 91 nets.
